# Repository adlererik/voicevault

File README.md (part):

# VoiceVault

**A dedicated encrypted voice device, being developed and tested in software before hardware is built.**

A phone can be an excellent communications modem and an unsafe place to handle a private conversation. VoiceVault explores a different boundary: put the microphone path, audio codec, encryption keys, verified contacts and call approval inside a separate device. Give the phone encrypted media to forward.

The intended adversary has **NSA-class capabilities**: both phones may already be completely compromised through Pegasus-like spyware, zero-day or zero-click exploits, and telecommunications and relays may be controlled by the attacker. **Supply-chain attacks are excluded from the current threat model.** The project starts after phone compromise; it does not attempt to prevent or reproduce the exploit that compromised the phone.

**Today:** working Rust voice simulations, hostile-phone processes, lifecycle security models, a live device-and-test dashboard and a linked Cortex-M33 diagnostic. **Destination:** a small independent voice endpoint with its own trusted display, wired headset audio, battery, inductive charging and a carefully isolated BLE connection to a phone. No physical VoiceVault device has been built.

[Project vision](docs/PROJECT_VISION.md) · [Architecture](docs/ARCHITECTURE.md) · [Threat model](docs/THREAT_MODEL.md) · [Every security control](docs/SECURITY_CONTROLS.md) · [Why these algorithms](docs/CRYPTOGRAPHY.md) · [Test evidence](docs/RESULTS.md) · [Hardware roadmap](docs/ROADMAP.md) · [Hybrid call security](docs/POST_QUANTUM.md)

## Hardware laboratory

The active **[standalone B0 design](hardware/rev-b/README.md)** is a custom **70 × 45 mm SMD PCB** using the identified Safe 7 core ICs, plus wired audio, physical microphone disconnect, offline microSD, trusted display/touch, battery/Qi circuits and separate MCU/radio debug interfaces. Native KiCad now contains **296 electrical components, 14 probe pads and four mounting holes**. KiCad is connected locally through MCP; **ngspice 47** runs the circuit experiments directly.

*Official FreeRouting 2.5.0 produced a complete-board SES checkpoint, imported into the live KiCad editor through kipy without changing any of the 314 placements. After copper refill, native KiCad reports 280 open connections, 33 layout errors and 100 warnings. [Actual routing result and DRC](hardware/evidence/2026-11-12/autoroute/README.md). Earlier checks cover MCU ball/function mapping and circuit correspondence; the circuit models include 799 passive/static cases. [Evidence and limits](hardware/evidence/2026-11-12/README.md)*

The subsequent [Quilter cloud trial](hardware/evidence/2026-11-13/quilter/routed-return/README.md) finished at **89% routed**, but native review with the original rules found **103 unfinished connections, 294 layout errors and 117 warnings**. It remains isolated for automatic repair and rerouting; it has not replaced the live board. Returned files, hashes, the screenshot and the complete native findings are preserved for review.

**Manufacturing remains blocked:** 280 connections remain unrouted and the latest native DRC failed. Exact sourcing and the HDI stackup need acceptance, and power/RF/audio/charging/isolation need physical qualification. The [circuit inventory](hardware/rev-b/circuit-inventory.csv) is not an approved JLCPCB BOM. [Cost comparison for four assemblies delivered to Sweden](hardware/rev-b/MANUFACTURING_COST.md). No board has been ordered or built. The earlier DK2 carrier and Nucleo assessment remain historical reference work in the [hardware laboratory](hardware/README.md).

## The idea: move the endpoint

An ordinary encrypted calling app processes plaintext on the phone. Once an attacker controls that operating system, network encryption alone cannot protect audio the operating system can already access.

VoiceVault's intended device owns the sensitive endpoint. Contacts are verified there, calls are approved there, and audio is encoded and encrypted there before reaching the phone. The phone carries encrypted records and necessary signaling; it does not become a trusted authority for identities, consent, keys, time, entropy or firmware.

This distinction depends on the physical audio path. The proposed host-phone arrangement includes removing its microphones and speakers, keeping voice on an external wired headset connected to VoiceVault, and validating remaining acoustic pickup paths. An unmodified compromised phone nearby can still record speech through its own microphone. [Why a separate device, and its limits](docs/DEVICE_RATIONALE.md)

*Architecture illustration. Analog audio and BLE are hardware targets; current calls use synthetic audio and bounded local IPC. Public signaling and transport metadata remain observable.*

## A real software foundation

The lab makes two endpoints conduct a simultaneous encrypted voice exchange through two hostile phone processes and a relay. It uses actual Opus and actual cryptography, produces recovered WAV files, injects delivery faults, and records results for inspection.

| Built and exercised | What it establishes |
|---|---|
| Two voice endpoints and three hostile transport processes | A concrete separation between trusted audio/key handling and untrusted delivery, under a trusted Linux host |
| Confirmed enrollment, pinned contacts and signed invitations | Explicit identity, consent, replay and accepted-call binding rules |
| Real Opus → Noise encryption → hostile transport → authentication → decode | An executable media pipeline, including loss and malformed-input handling |
| Stored-contact, entropy, radio and offline-update models | Testable device-local policy before selecting physical chips |
| The same trusted crates compiled without `std` and linked for Cortex-M33 | Functional CPU execution and measured memory fit under a named capacity budget |
| An event-backed dashboard with searchable individual results | Visible checks, named test outcomes, attack traces and saved replays |

A tested model is not a finished hardware protection. The [assurance case](docs/ASSURANCE.md) states which assumptions each result depends on.

## The threat model and the protections

The attacker may observe, drop, replay, modify, reorder, delay and inject traffic; collude across both phones and relays; impersonate contacts; flood ingress; and try to turn malformed messages into unauthorized device actions. The design also tests a malicious authenticated peer, because having a valid key does not make compressed audio harmless.

| Attack or failure | Protection in the software model | Boundary |
|---|---|---|
| Intercept or modify voice | ChaCha20-Poly1305 under authenticated Noise transport keys | Trusted endpoints and sound implementations are assumed |
| Substitute a peer during enrollment | Noise XX, signed identity/DH records, full transcript comparison and confirmation on both sides | Trusted local comparison is required; hardware UI is future work |
| Spoof a contact or call invitation | Pinned Ed25519 identity, recipient binding, boot challenge, expiry and persisted counters | Invitation metadata itself is not confidential |
| Reuse a different invitation for an authenticated call | The hybrid Noise prologue binds the signed offer and acceptance and both verified identities | Local approval remains separate from remote signaling |
| Save encrypted calls for future quantum decryption | Fresh X25519 and ML-KEM-768 establish each call, with the hybrid suite required | Depends on the hybrid construction, trusted endpoints and erasure |
| Replay media or poison the replay window | Monotonic sending, directional keys, authenticated counter/slot checks and a bounded replay bitmap | Invalid input cannot commit incoming replay state |
| Activate audio through the phone | Local consent plus encrypted Confirm/Ready; no radio mic/consent opcode | Actual headset and physical disconnect still need validation |
| Infer speech or silence from record length | CBR Opus, DTX off, fixed 128-byte records and encrypted filler | Call boundaries, timing errors, location and correlation remain visible |
| Exhaust queues or force a burst after a stall | Bounded ingress, assembly and jitter queues; expiry; absolute deadlines; missed slots discarded | A hostile network can still deny service |
| Roll back stored contacts or signaling counters | Owner-bound AEAD snapshots tied to a protected monotonic generation | Protected storage is modeled, not a chip driver |
| Push firmware through the phone | No remote updater; locally authorized signed-image policy | Physical boot/update enforcement remains future hardware work |
| Install an old, corrupt or wrong-device image | Target/version/hash/signature checks, protected floor, two banks and readback | Real flash and counter atomicity are unmeasured |
| Interrupt an offline update | Preserve the active bank, write header last, verify before boot/version handoff | Tests cover modeled write cuts and selected torn writes |
| Weaken randomness through the phone | Onboard-only entropy-source interface, failure checks and two-source policy | Hardware entropy quality and independence need measurement |
| Keep using a closed or expired session | Irreversible close, owned key destruction, bounded media epoch and fresh handshake | Complete erasure and seamless renewal remain open |

The [complete control register](docs/SECURITY_CONTROLS.md) links each protection to its code, evidence, assumptions and remaining hardware work.

## Why these cryptographic choices?

| Choice | Role and reason |
|---|---|
| **X25519** | Compact Diffie–Hellman key exchange with fresh per-call ephemeral secrets; separate from signing identities |
| **ML-KEM-768** | Adds a fresh post-quantum secret for each call using the portable `libcrux-ml-kem` implementation |
| **Ed25519** | Signed identities, contact bindings, invitations and offline-image authorization |
| **ChaCha20-Poly1305** | Established authenticated encryption for voice and stored snapshots; suitable for portable software implementations |
| **BLAKE2s** | A 32-bit-oriented hash for the selected Noise suite, domain-separated bindings and firmware digests |
| **Noise's HMAC/HKDF-BLAKE2s** | An established transcript-bound key schedule and separate transport keys for each direction |
| **Noise XX / KKhfs through Snow** | XX for first enrollment and the experimental hybrid KK modifier for calls between pinned contacts |
| **Opus** | Practical speech compression; hard CBR and no DTX work with the outer fixed-size envelope |
| **Rust with `no_std` integration** | Safe parsing/state code and bounded interfaces that can migrate toward embedded firmware |

The hybrid suite is required for new calls. Both peers authenticate the full exchange and its algorithm suite before local consent and encrypted confirmation open audio. ML-KEM-768 is an explicit exception to the owner’s preference to avoid NIST algorithms where practical. [Protocol and wire format](docs/POST_QUANTUM.md) · [Cryptographic rationale](docs/CRYPTOGRAPHY.md)

## Evidence you can inspect

The hybrid v2 run on **2026-11-11** passed **all 11 required groups and 48 checks**. The suite recorded 68 named outcomes, including five bounded Kani checks, and ran eight fuzz campaigns for at least 120 seconds each. It also checked 80 ML-KEM-768 vectors. The altered-startup scenario verifies that a compromised phone cannot open either audio path by modifying the key exchange.

| Recorded result | Observation |
|---|---|
| Real encrypted audio | Both directions recovered generated audio through two hostile phone processes and a relay |
| Cortex-M33 execution | Hybrid startup, fragmentation and 32 Opus frames executed in QEMU |
| Linked image and observed stack | 863,104 bytes of a 983,040-byte slot and 84,876 bytes of a 131,072-byte stack reserve |
| Reference memory budget | 37,500 bytes unassigned after static state and stack/display/driver reservations |

[Latest raw results](docs/evidence/hybrid-v2/) · [What each fuzz target tests](docs/FUZZING.md) · [All recorded runs](docs/RESULTS.md) · [Embedded fit](docs/PLATFORM.md)

*Actual dashboard capture during hybrid handshake fuzzing. The device panels show the earlier live call in the same run. [Live call capture](docs/screenshots/command-deck-live-laptop.png) · [Historical full-suite completion](docs/screenshots/voicevault-complete.png)*

## See what is happening as it happens

The UI opens at **http://127.0.0.1:8765/** for every run. Two device panels show identity/contact verification, invitation authentication, call establishment, encrypted media, receiver rejection and audio playout/concealment. Both hostile phones and the relay are shown between them. The test area reports every scheduled check, individual Rust tests, all twelve Opus vectors, each bounded proof and actual fuzzing counters as their harnesses report them.

`./lab demo --seconds 30` gives two visible 30-second normal/fault calls. Click **Listen live** to monitor actual decoded synthetic tones. Choose either receiver or both; sound is off by default. Device cards, graphical phones, packet/rejection flashes, a recent-event ticker and compact check/fuzz displays now occupy the top observation deck. `./lab watch` runs the complete verification suite; `./lab ui` reopens the persistent page. Refresh reconstructs the current run, reconnect resumes events, and a new published run resets the display. Compilation, proofs and fuzzing are shown as checks rather than invented device traffic. Scored timing keeps graphics still and labels its buffered packet traces recorded. A running test is never displayed as a pass merely because it started. [How the dashboard works](docs/LIVE_DASHBOARD.md)

## Toward the physical device

The intended device has a trusted color display and controls, analog headset jack, independent battery, inductive charging and a separate BLE controller. Persistent secrets and protected state should use appropriate secure-element capabilities. A small protected first-stage verifier and physically initiated offline updates are part of the intended boot design. The inspiration is the Safe 7 separation of host and sensitive operations; this is an independent voice design with different workloads and requirements.

The next hardware work is to finish the standalone B0 placement and routing, review power/clock/RF/return paths, finalize exact sourcing and prepare a controlled bring-up plan. Focused simulations guide the measurements needed on physical prototypes. Real-time audio, radio containment, hardware entropy, durable storage, trusted UI and acoustic leakage need physical evidence. Decentralized signaling, possibly through interchangeable Nostr relay adapters, remains a future investigation. The proposed clear glitter enclosure and signed reference photos are separate physical tamper-evidence research.

[Device vision](docs/PROJECT_VISION.md) · [Hardware comparison](docs/DEVICE_RATIONALE.md) · [Safe 7 reference and prototype plan](docs/HARDWARE_PLAN.md) · [Roadmap and decision gates](docs/ROADMAP.md)

## Try the software lab

```sh
git clone https://github.com/adlererik/voicevault.git
cd voicevault
./lab help
./lab demo
./lab watch --out /absolute/path/to/an/empty/directory
./lab ui       # reopen the same persistent local dashboard
./lab status
./lab replay
```

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
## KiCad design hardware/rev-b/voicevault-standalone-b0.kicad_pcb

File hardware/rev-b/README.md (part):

# VoiceVault standalone prototype B0

**Routing in progress — not a working or fabrication-ready PCB.**

[Quilter routing and native review (13 November)](QUILTER_ROUTING.md): the full cloud trial finished at 89% routed. Native review found 103 unfinished connections, 294 layout errors and 117 warnings, so the result is isolated for repair and has not replaced the live PCB. Six placement candidates, input hashes and rejected experiments are also preserved.

VoiceVault moves plaintext voice, keys, contacts and call approval into a dedicated device. An already compromised phone carries encrypted records over BLE. This custom rectangular SMD board uses the identified **Trezor Safe 7 TS7 rev_D core ICs**, with added wired headset audio, physical microphone disconnect, offline microSD and separate computer-debug connections. It replaces the earlier development-board carrier as the active hardware design.

The current native KiCad project contains **296 electrical components, 14 board-only probe pads and four mounting holes** on a provisional **70 × 45 mm**, six-layer, 1.0 mm board. Components are placed on both sides. The latest complete-board autorouter checkpoint **fails native DRC: 280 connections remain unrouted, with 33 layout errors and 100 warnings**; exact sourcing and HDI stackup are unresolved, and no physical board has been tested. [Machine-readable status](STATUS.json) · [Recorded evidence and images](../evidence/2026-11-12/README.md)

*Native KiCad exports, front and rear. RF copper and ground pours are present; most signal and power routing remains incomplete.*

## Open and inspect

From the repository root, run `./hardware/open`. The launcher opens one PCB editor and reuses it to limit memory use. Open `voicevault-standalone-b0.kicad_pro` in KiCad to inspect the root schematic and its **18 child sheets**. Keep the large schematic/3D viewers closed when running routing studies on this computer.

KiCad 10.0.8 uses the local `voicevault-kicad` MCP connection through its official IPC API. Circuit simulation uses **ngspice 47 directly**, preserving actual netlists, logs and measurements. MCP is useful for editor interaction; it is not required to run a command-line simulator. [Tool setup](../README.md)

```sh
./hardware/check --design-only --spice
```

This runs native schematic/pad/net checks, ST ball/function comparisons, ERC/DRC, an antenna-rule negative control, **799 ngspice model cases**, and the explicit power-allocation study. Exit 0 with `--design-only` means the available checks passed. The report still says **manufacturing blocked**. Without that option, exit 2 preserves the blocked release verdict. Exit 1 means a check failed. The historical carrier checks remain available as `./hardware/check --rev-a --design-only`.

## Circuit architecture

| Area | Current circuit intent |
|---|---|
| Trusted compute | STM32U5G9ZJJ6Q, UFBGA144, with local clocks, reset, decoupling and internal-SMPS network. The local symbol restores two power balls missing in the installed library. All 144 ball names and 29 selected peripheral functions are compared with separately pinned ST data. |
| Power and battery | nPM1300 dual 200 mA bucks/charger; USB power-only entry, diode-isolated Qi entry, protected battery connector and external cell-temperature input. USB has no D+/D− contacts. Charging configuration and thermal qualification remain open. |
| Secure elements | TROPIC01 and OPTIGA Trust M on MCU-only buses with local power gates. These circuits do not demonstrate lifecycle configuration, entropy quality or secret protection on real silicon. |
| Hostile radio boundary | nRF52832-CIAA with separate SWD and radio power, fixed-direction SN74AXC4T774 bridges, reset control and default-disabled interface. UART carries bounded records; the radio has no audio, secure-element or MCU-debug wires. Electrical fault containment still needs bench tests. |
| Voice | TLV320AIC3204, SAI1 full duplex, dedicated switched audio regulator, CTIA 3.5 mm headset jack, headphone DC-blocking networks, ESD parts and a physical microphone disconnect. All codec controls stay on the trusted MCU side. |
| Trusted interface | Newhaven 240 × 320 display/touch candidate, local reset/update buttons and DRV2624 haptic driver. These require new VoiceVault drivers; this is not the Safe 7 private display assembly. |
| Offline updates | Locally powered microSD SPI interface with default-disabled signal bridge. Signed-image, rollback and interrupted-update policies exist in the software model; they have not been ported and qualified as this board's boot/update firmware. |
| Qi | STWLC38 receiver, coil resonance/rectifier components, thermal sensing and disable path. Its host-control bus is separate from PMIC and secure-element buses. Matching, configuration, charging and temperature behavior are unqualified. |
| NFC | ST25R3916B with dedicated regulator, bridges and matching network; default-off intent. Firmware must require an explicit local enrollment action. An NFC transport is not itself proof of contact identity. |
| Bench access | Main STDC14 and independent Nordic SWD headers, 14 probe pads and removable audio-current link. Prototype debug access deliberately exposes memory/firmware to trusted lab equipment. |

Read [circuit and power review](CIRCUIT_REVIEW.md), [computer connection and bring-up](DEBUG_AND_BRINGUP.md), and [display/battery adaptations](DISPLAY_BATTERY_CANDIDATES.md) before hardware work.

## Exact reference and differences

The source is pinned to trezor/trezor-hardware commit `d99ad42320a19875c124445195fa56f0dbaff6db`. The actual Safe 7 MCU is **STM32U5G9ZJJ6Q in UFBGA144**, not the LQFP144 STM32U5G9ZJT6Q on the DK2 reference board. The earlier DK2 pin allocations and hardware measurements cannot be assumed to apply to this PCB. Actual silicon revision is not yet verified.

The ten core selections are STM32U5G9ZJJ6Q, nPM1300-CAAA, TPS3420DDRYR, STWLC38JRM, nRF52832-CIAA, ST25R3916B-BWLT, SLS32AIA010MKUSON10XTMA2, TPS61062YZFR, DRV2624YFFR and the TROPIC01 family. TPS61062's `R` suffix selects tape/reel packaging. **TROPIC01's orderable silicon/provisioning revision remains unresolved. OPTIGA's reference order code is NRND.** [Core source table](core-parts.csv)

The published Safe 7 release contains PDFs and board views; it does not supply a complete editable manufacturing project or its private display/battery assemblies. This is a new VoiceVault layout, with catalogue display/battery candidates and added audio/card/debug circuitry. AO3401A power-gate FETs are an explicit adaptation from the reference CSD25501F3. New crystals, antenna/coil geometry, power loads and enclosure need their own validation. No Trezor factory identities, attestation keys or certification are reproduced.

## What the evidence establishes

The native export and actual PCB pads agree for 1,026 schematic-connected nodes and 124 intentional NC pins. The schematic's 323 exported net records include those virtual NC records; the PCB has **199 named copper nets**. The saved pre-autoroute check had zero ERC issues and zero layout violations. After the complete-board SES import and copper refill, native KiCad reports **280 open connections, 33 layout errors and 100 warnings**. The detailed list and independent full ratsnest both report 280. [Final native result](../evidence/2026-11-12/autoroute/README.md).

The antenna restriction is tested on a copy: headless KiCad rejects an unrelated track and a ground via inside the reserved area, and permits the RF-feed track. The live design is checked to remain unchanged. This verifies a CAD rule, not antenna performance or isolation from a physical attacker.

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
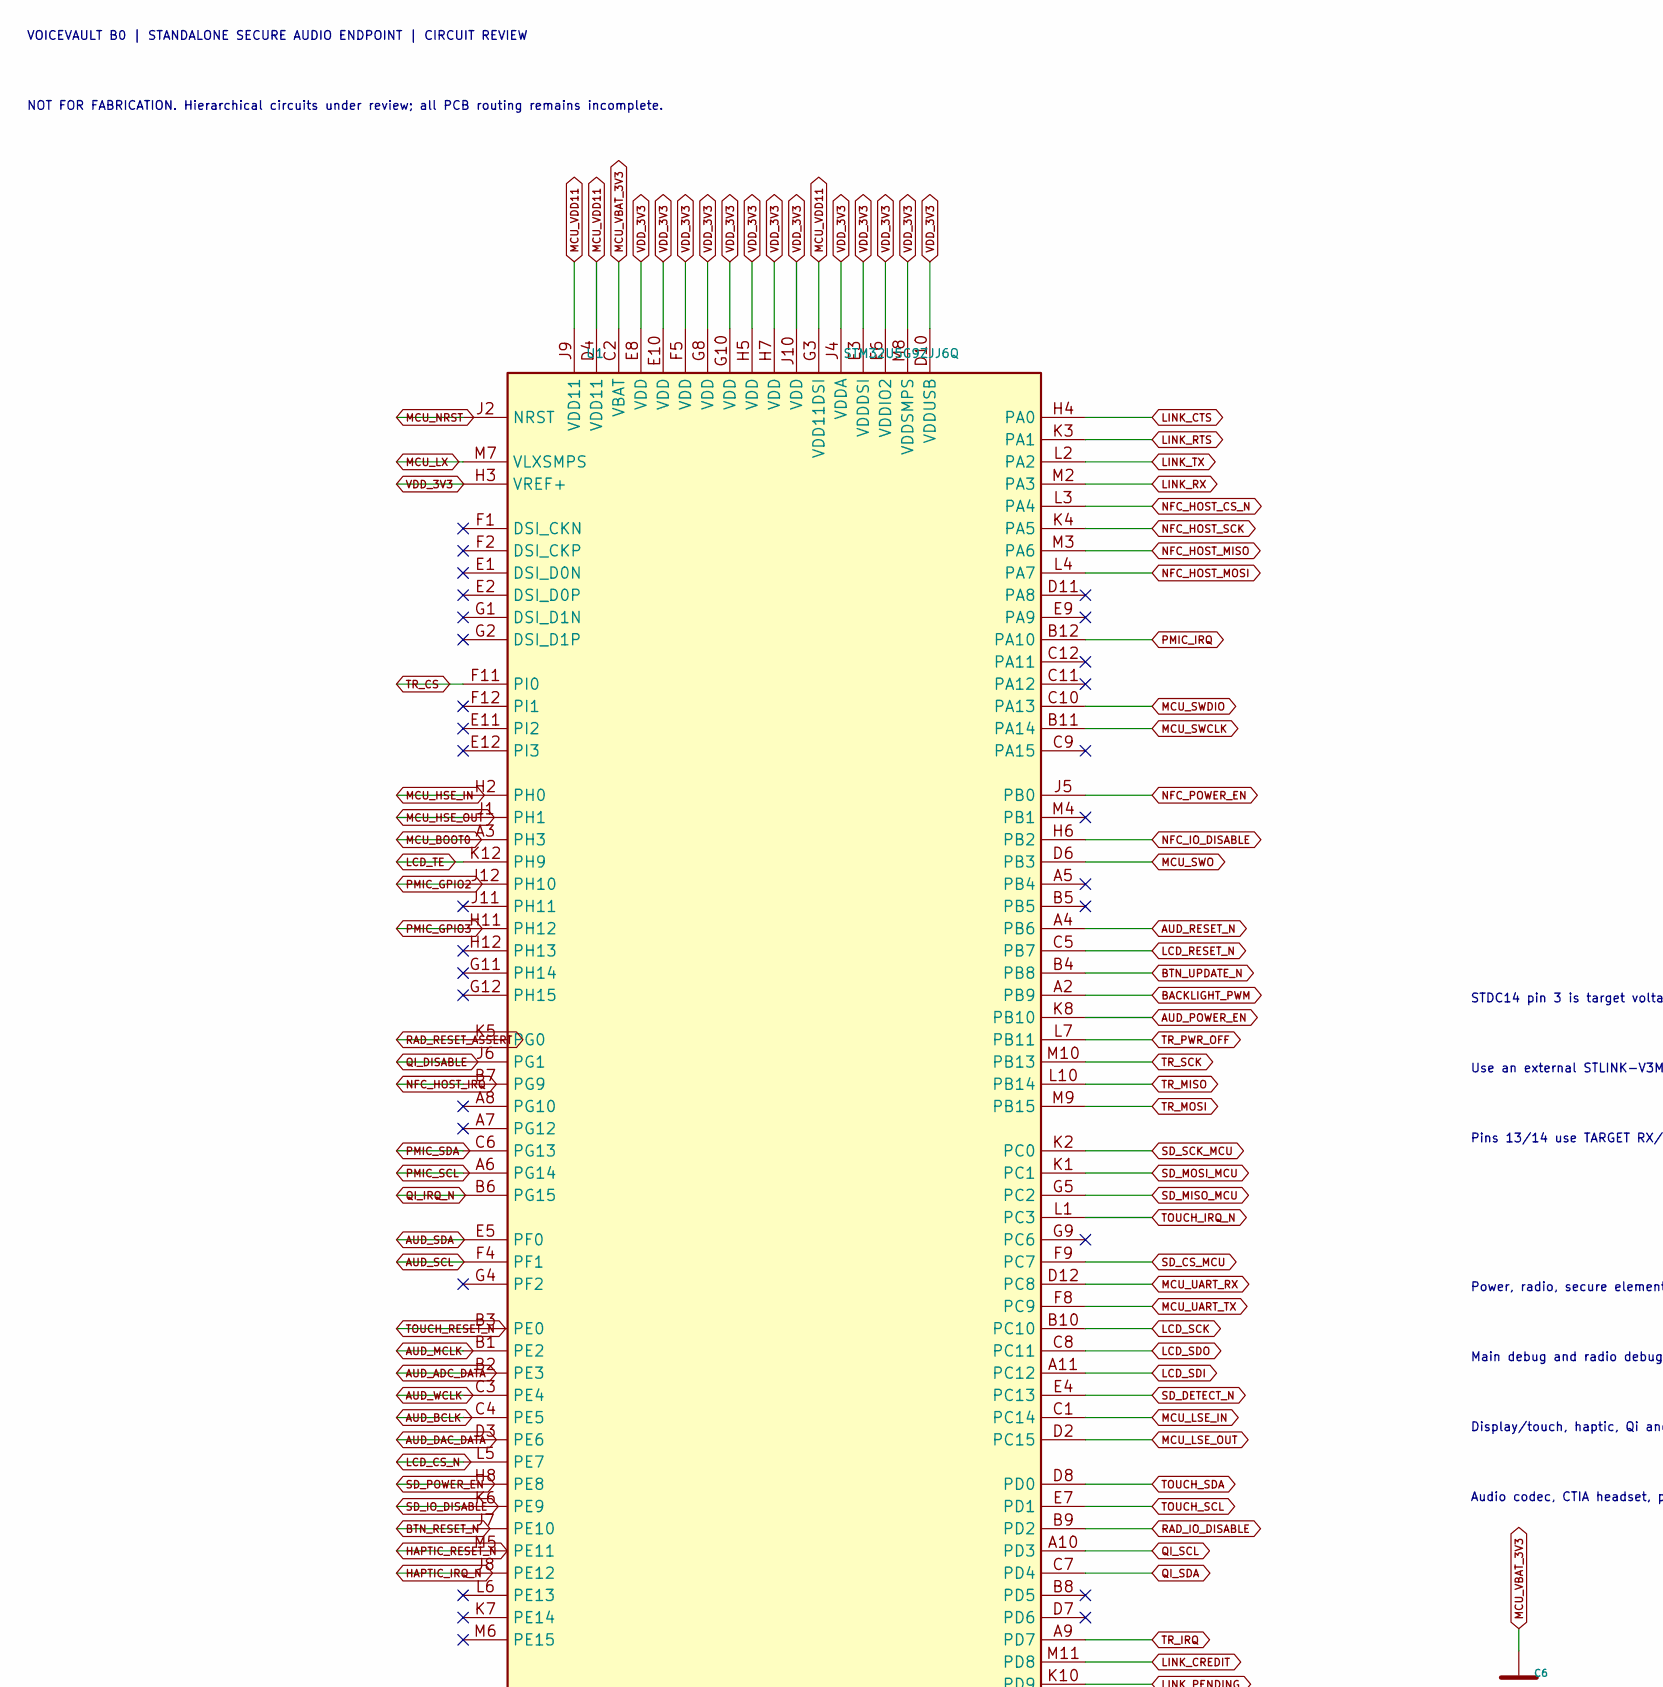
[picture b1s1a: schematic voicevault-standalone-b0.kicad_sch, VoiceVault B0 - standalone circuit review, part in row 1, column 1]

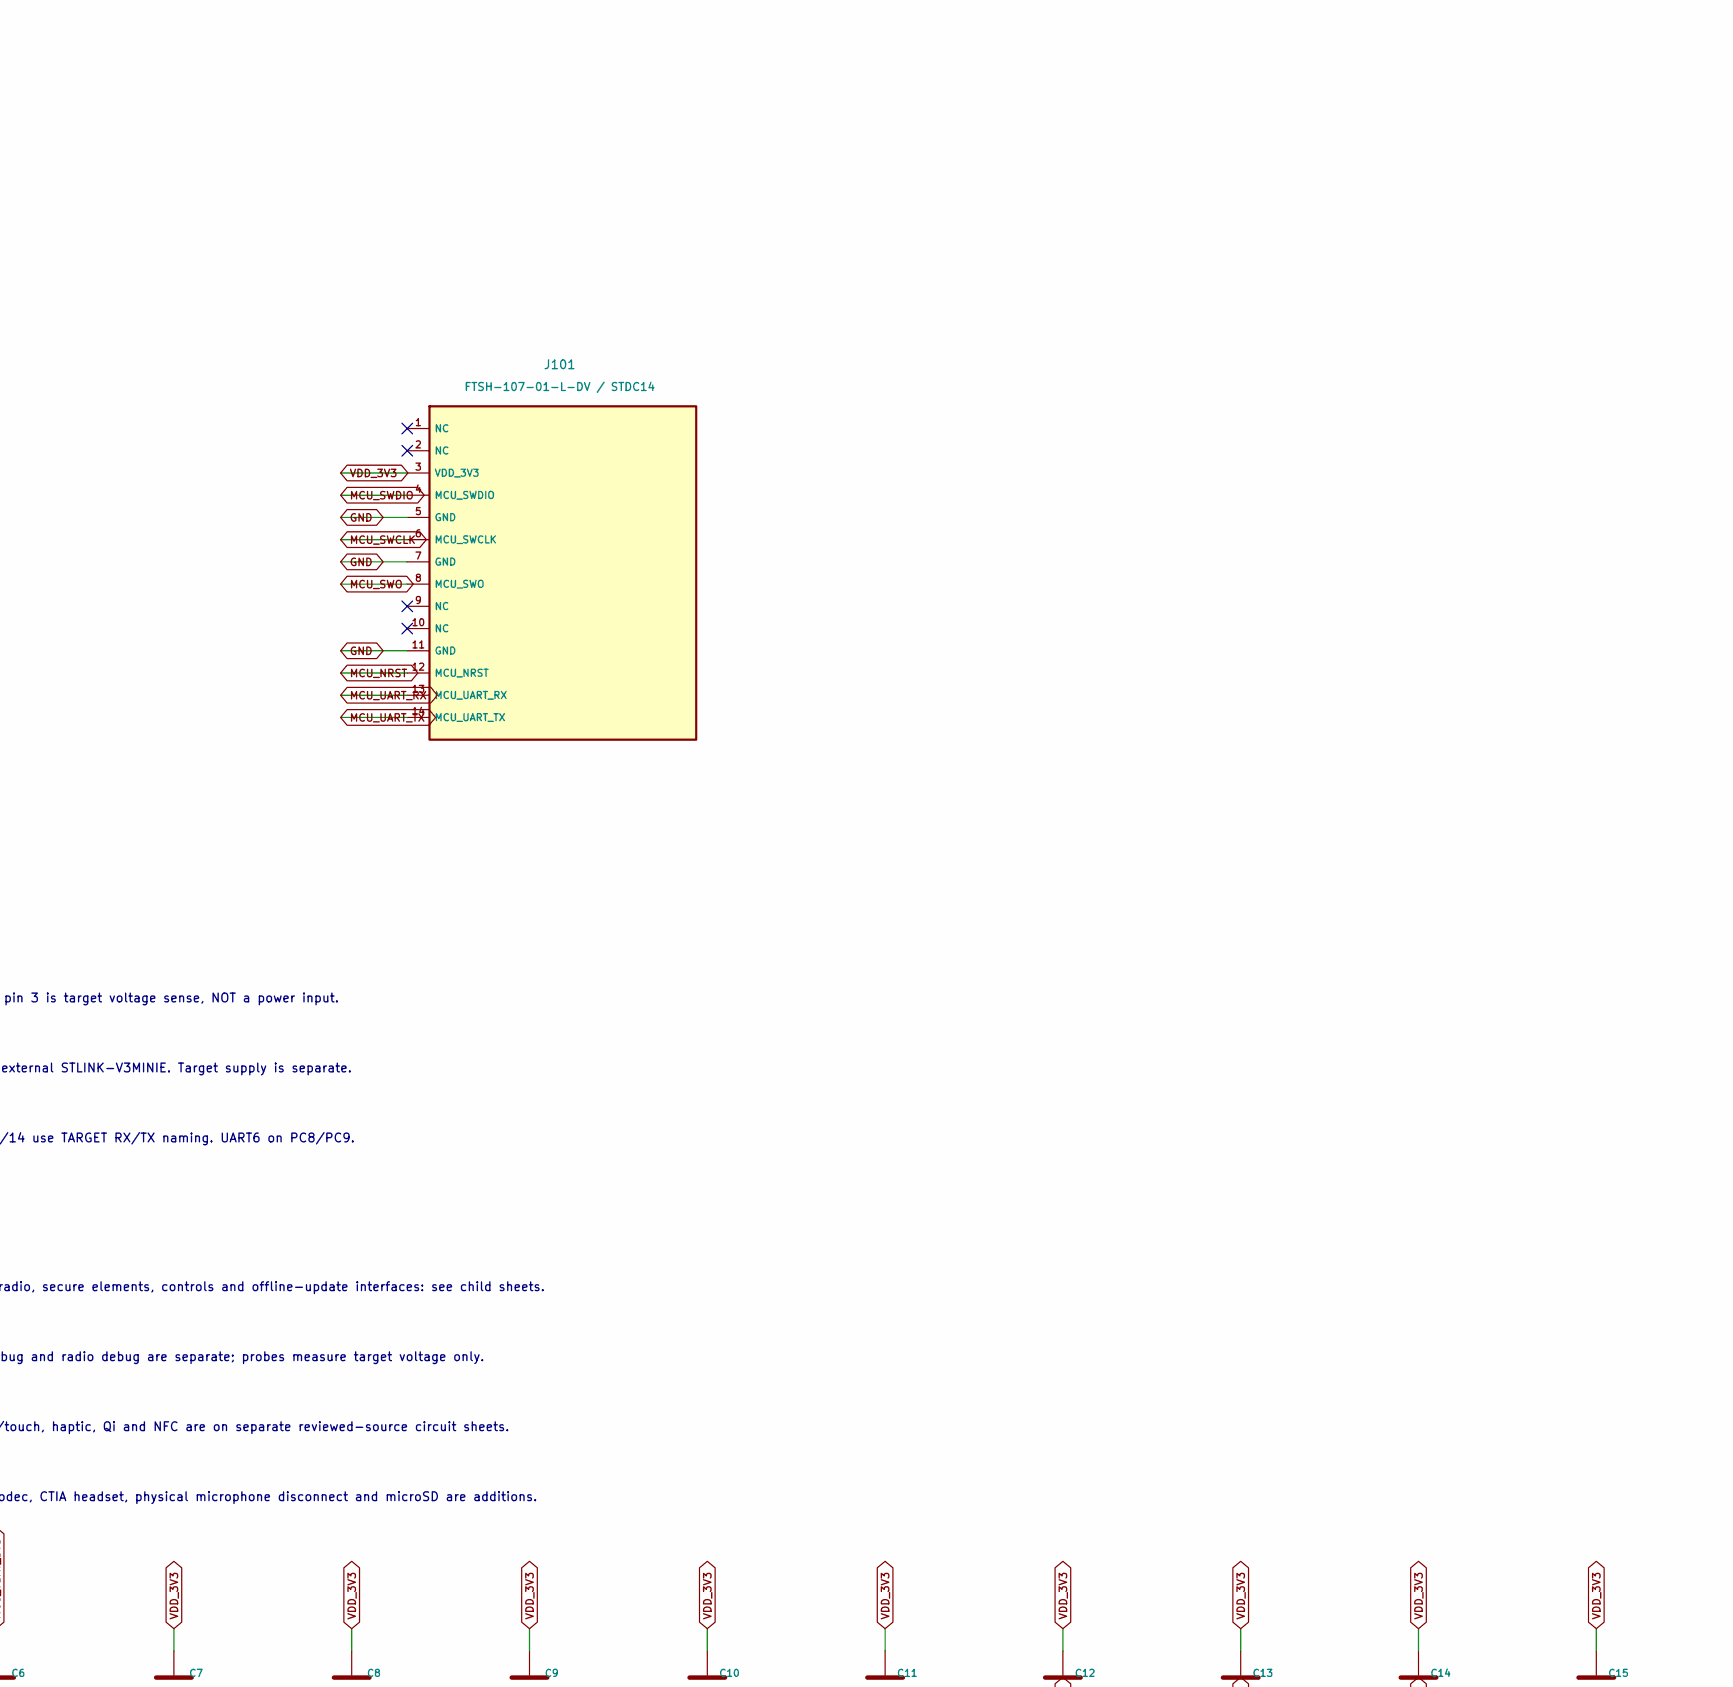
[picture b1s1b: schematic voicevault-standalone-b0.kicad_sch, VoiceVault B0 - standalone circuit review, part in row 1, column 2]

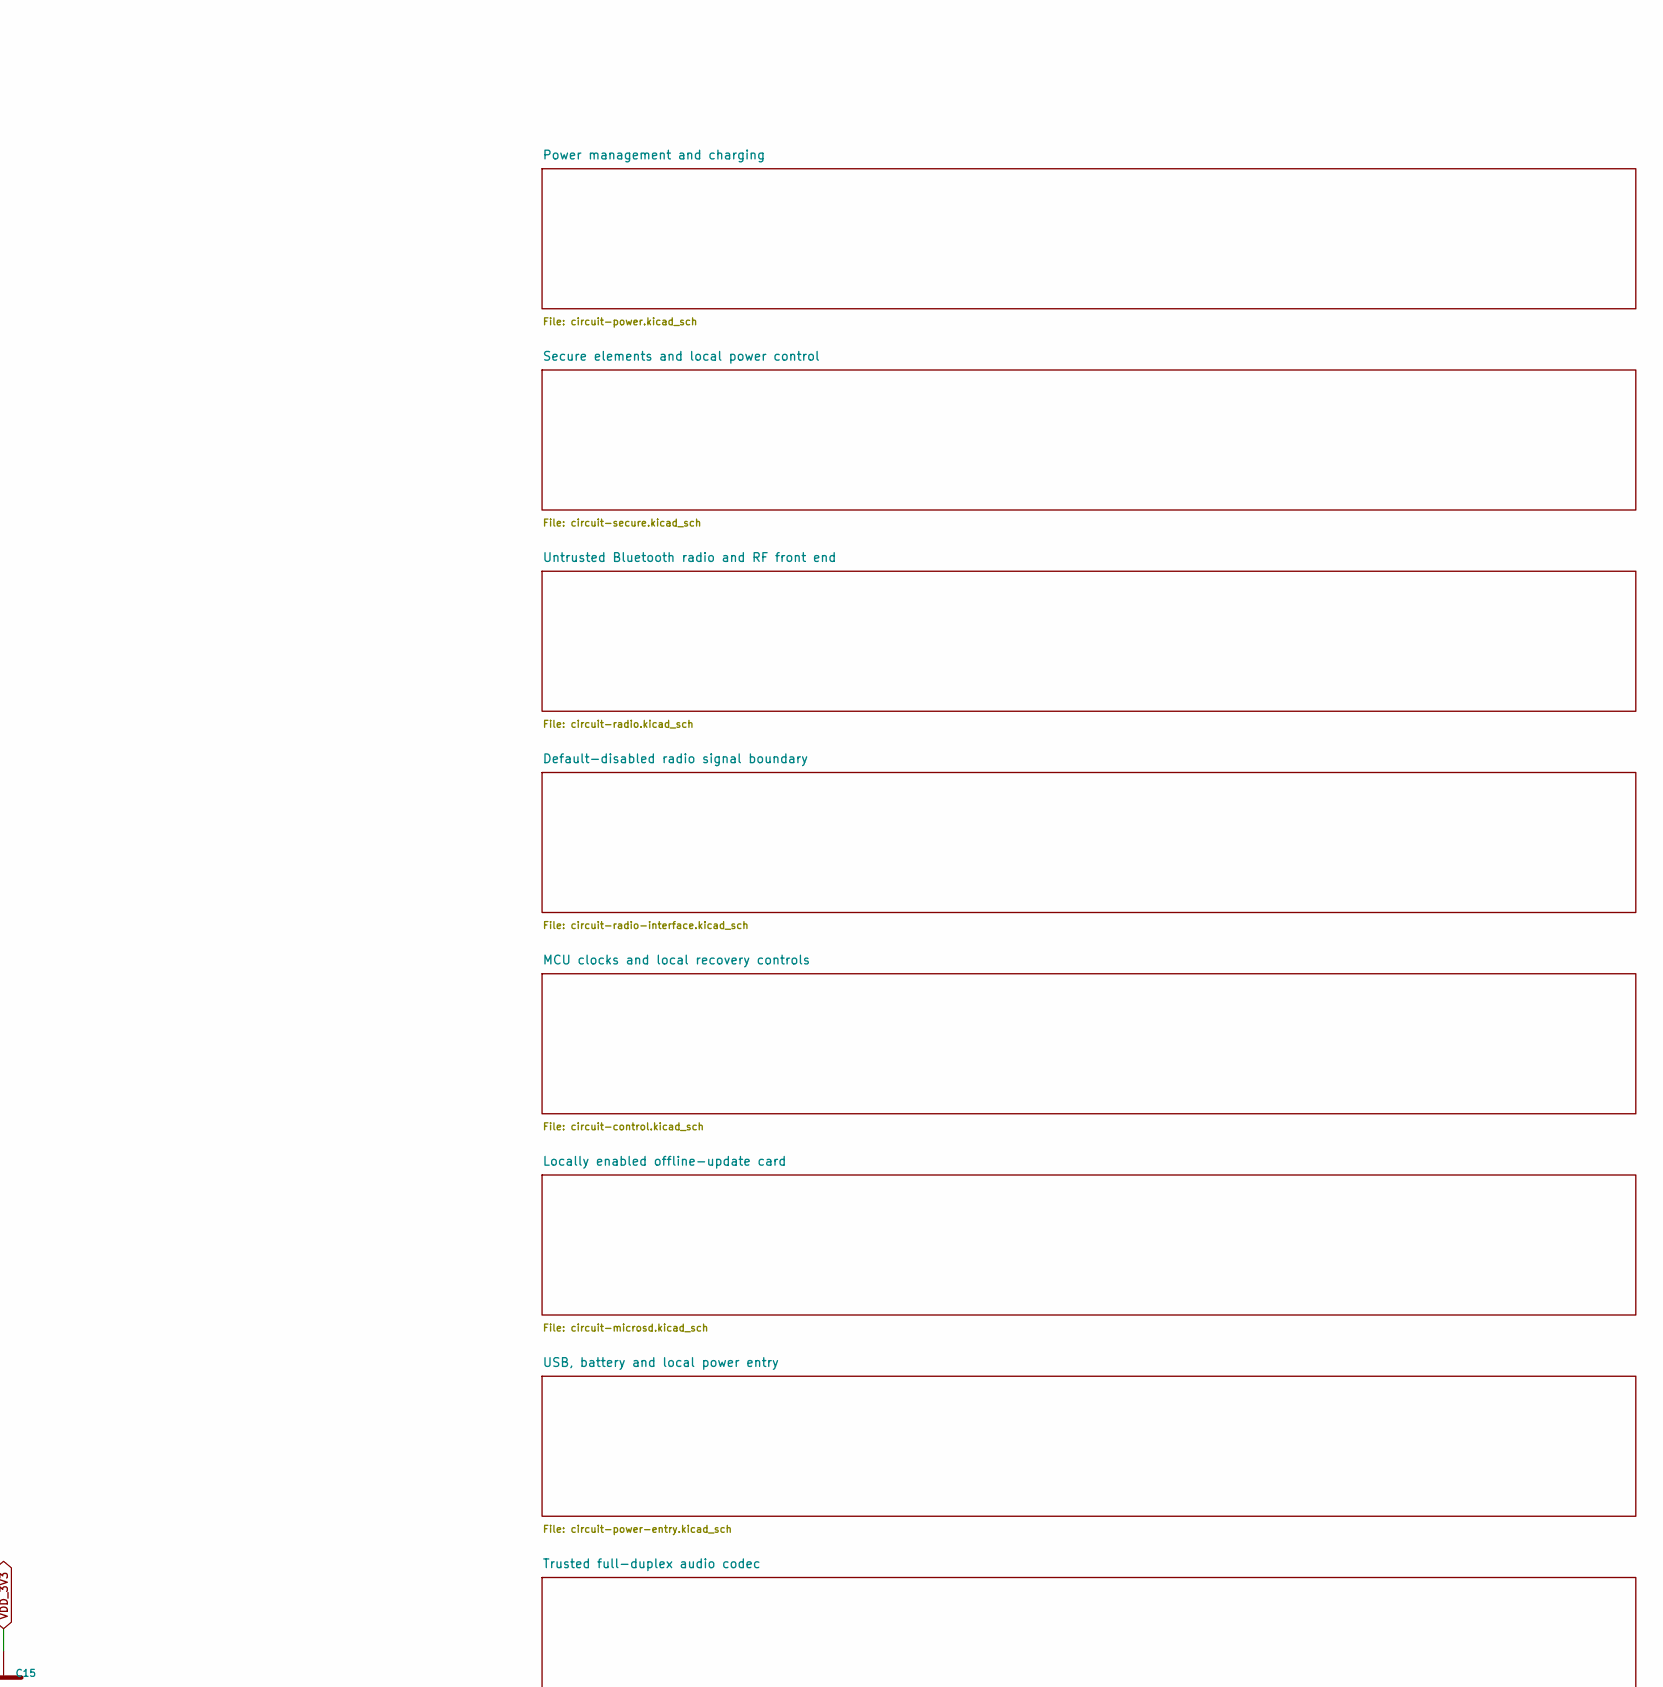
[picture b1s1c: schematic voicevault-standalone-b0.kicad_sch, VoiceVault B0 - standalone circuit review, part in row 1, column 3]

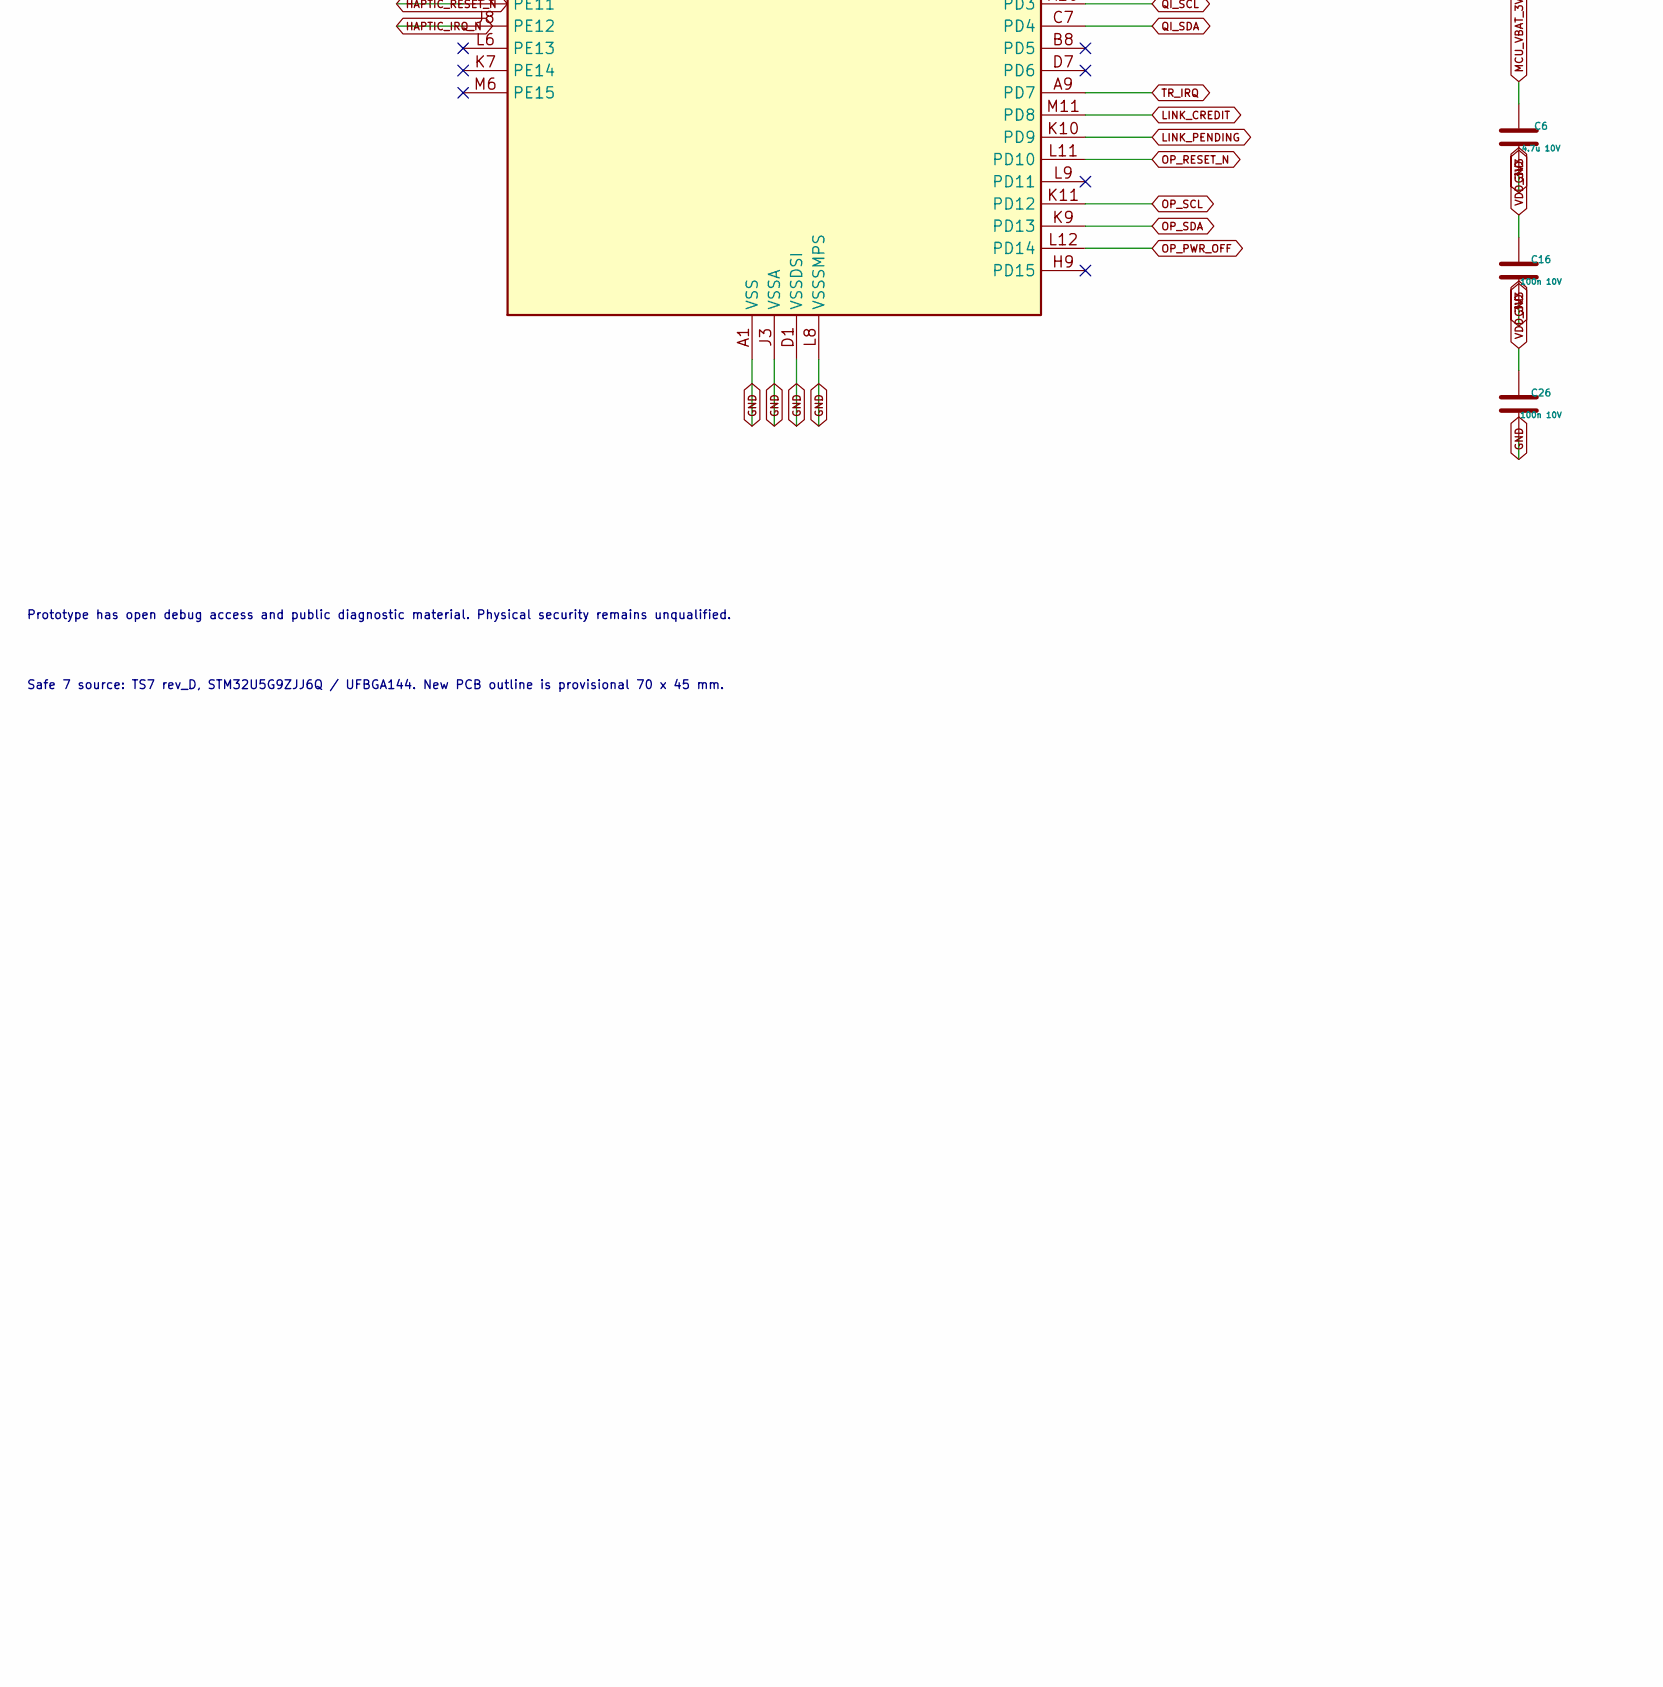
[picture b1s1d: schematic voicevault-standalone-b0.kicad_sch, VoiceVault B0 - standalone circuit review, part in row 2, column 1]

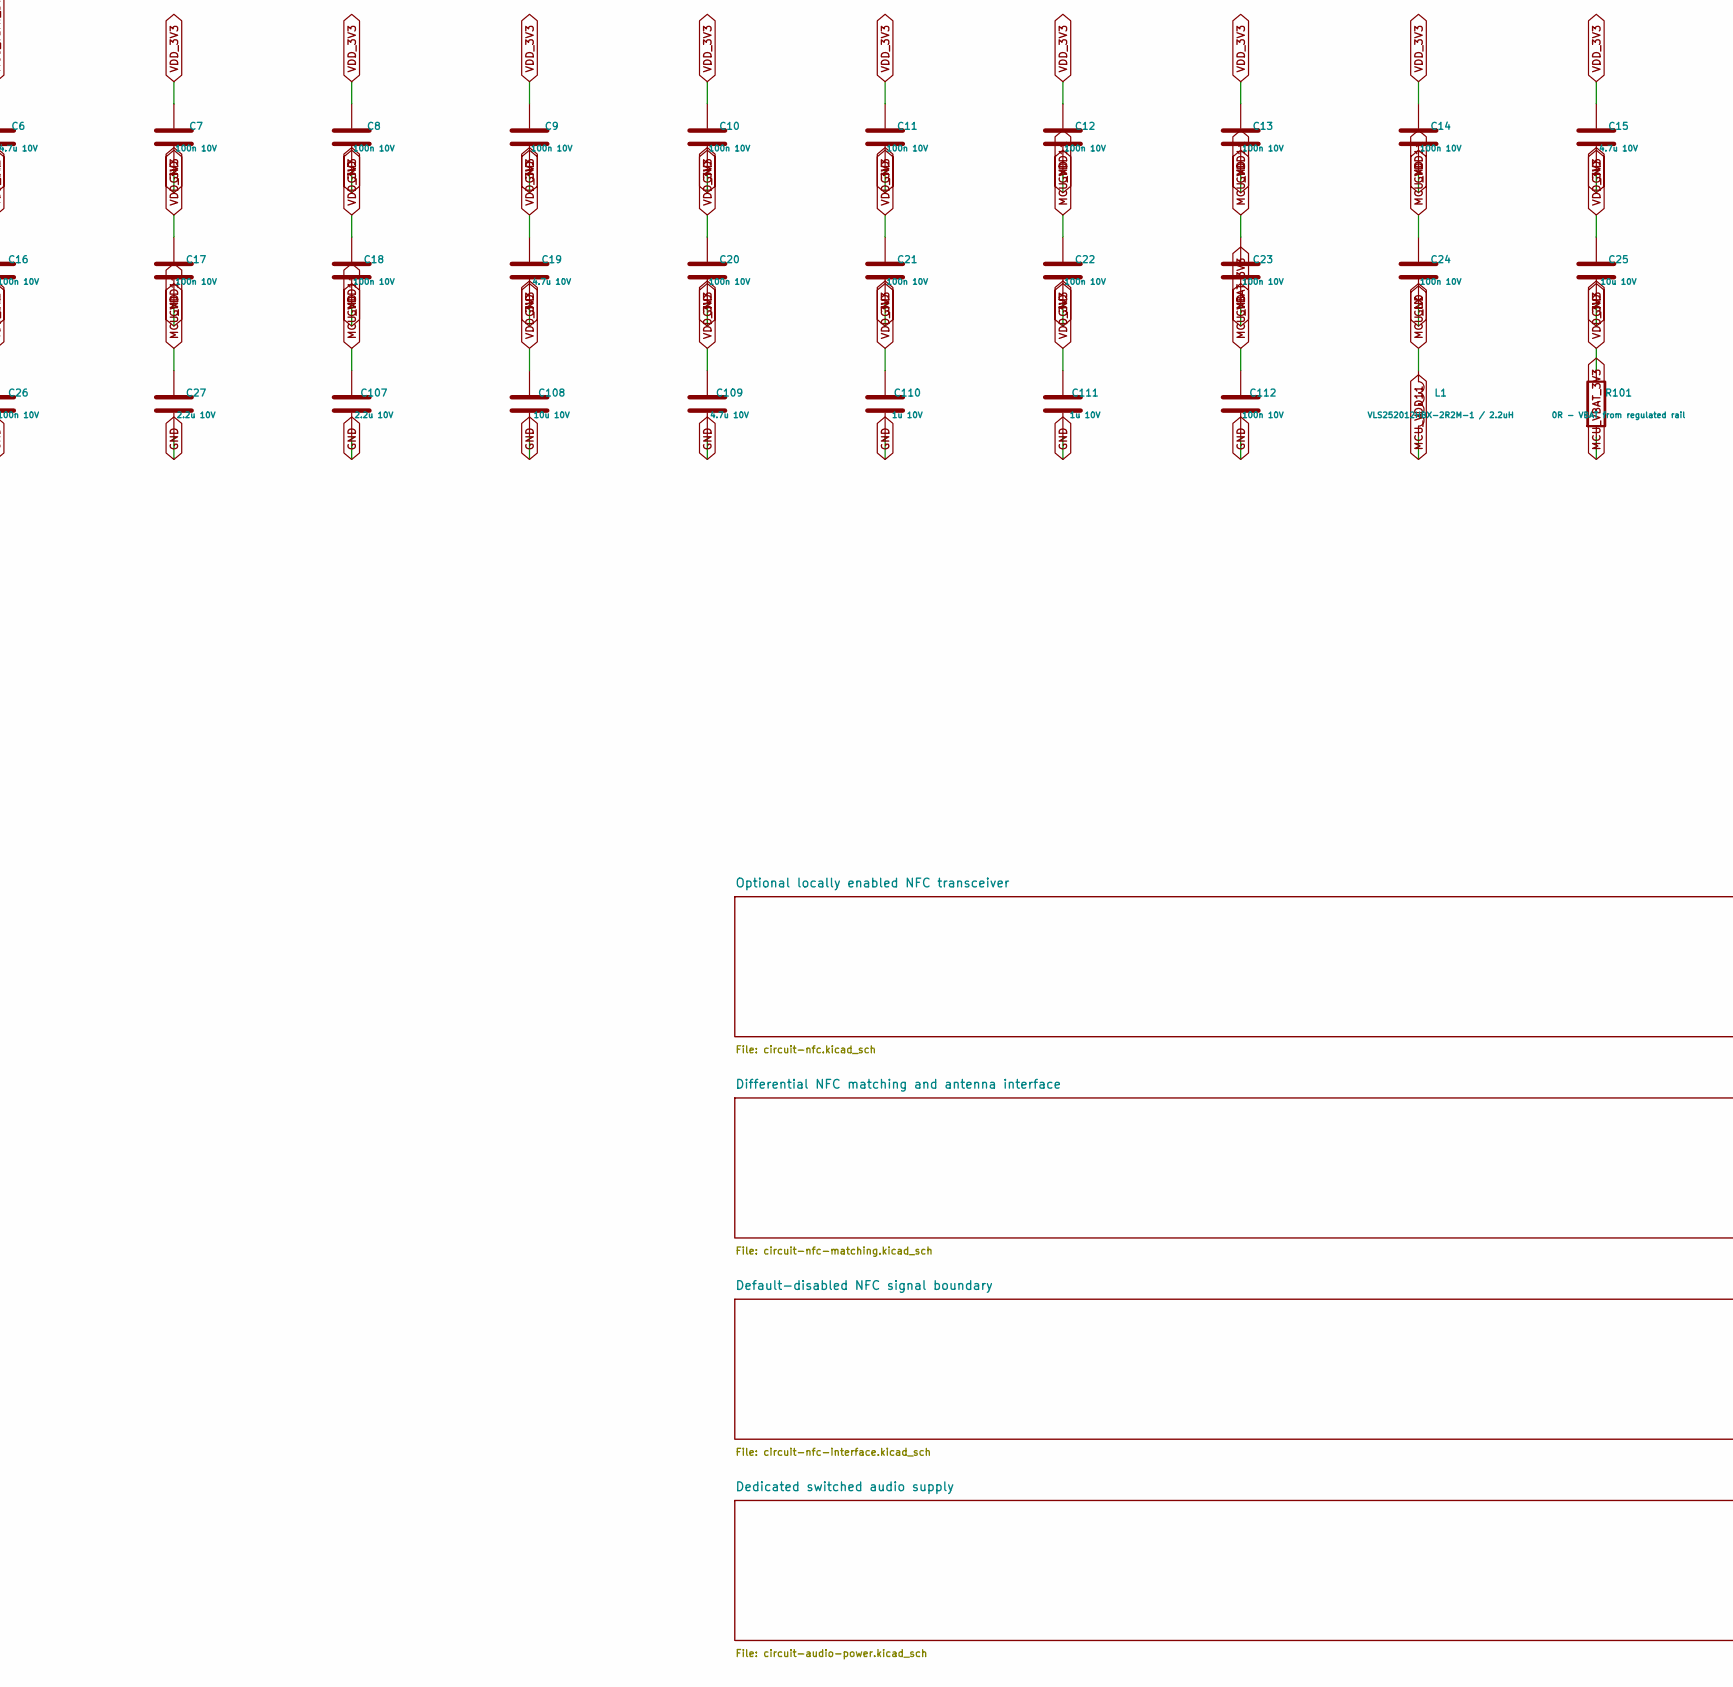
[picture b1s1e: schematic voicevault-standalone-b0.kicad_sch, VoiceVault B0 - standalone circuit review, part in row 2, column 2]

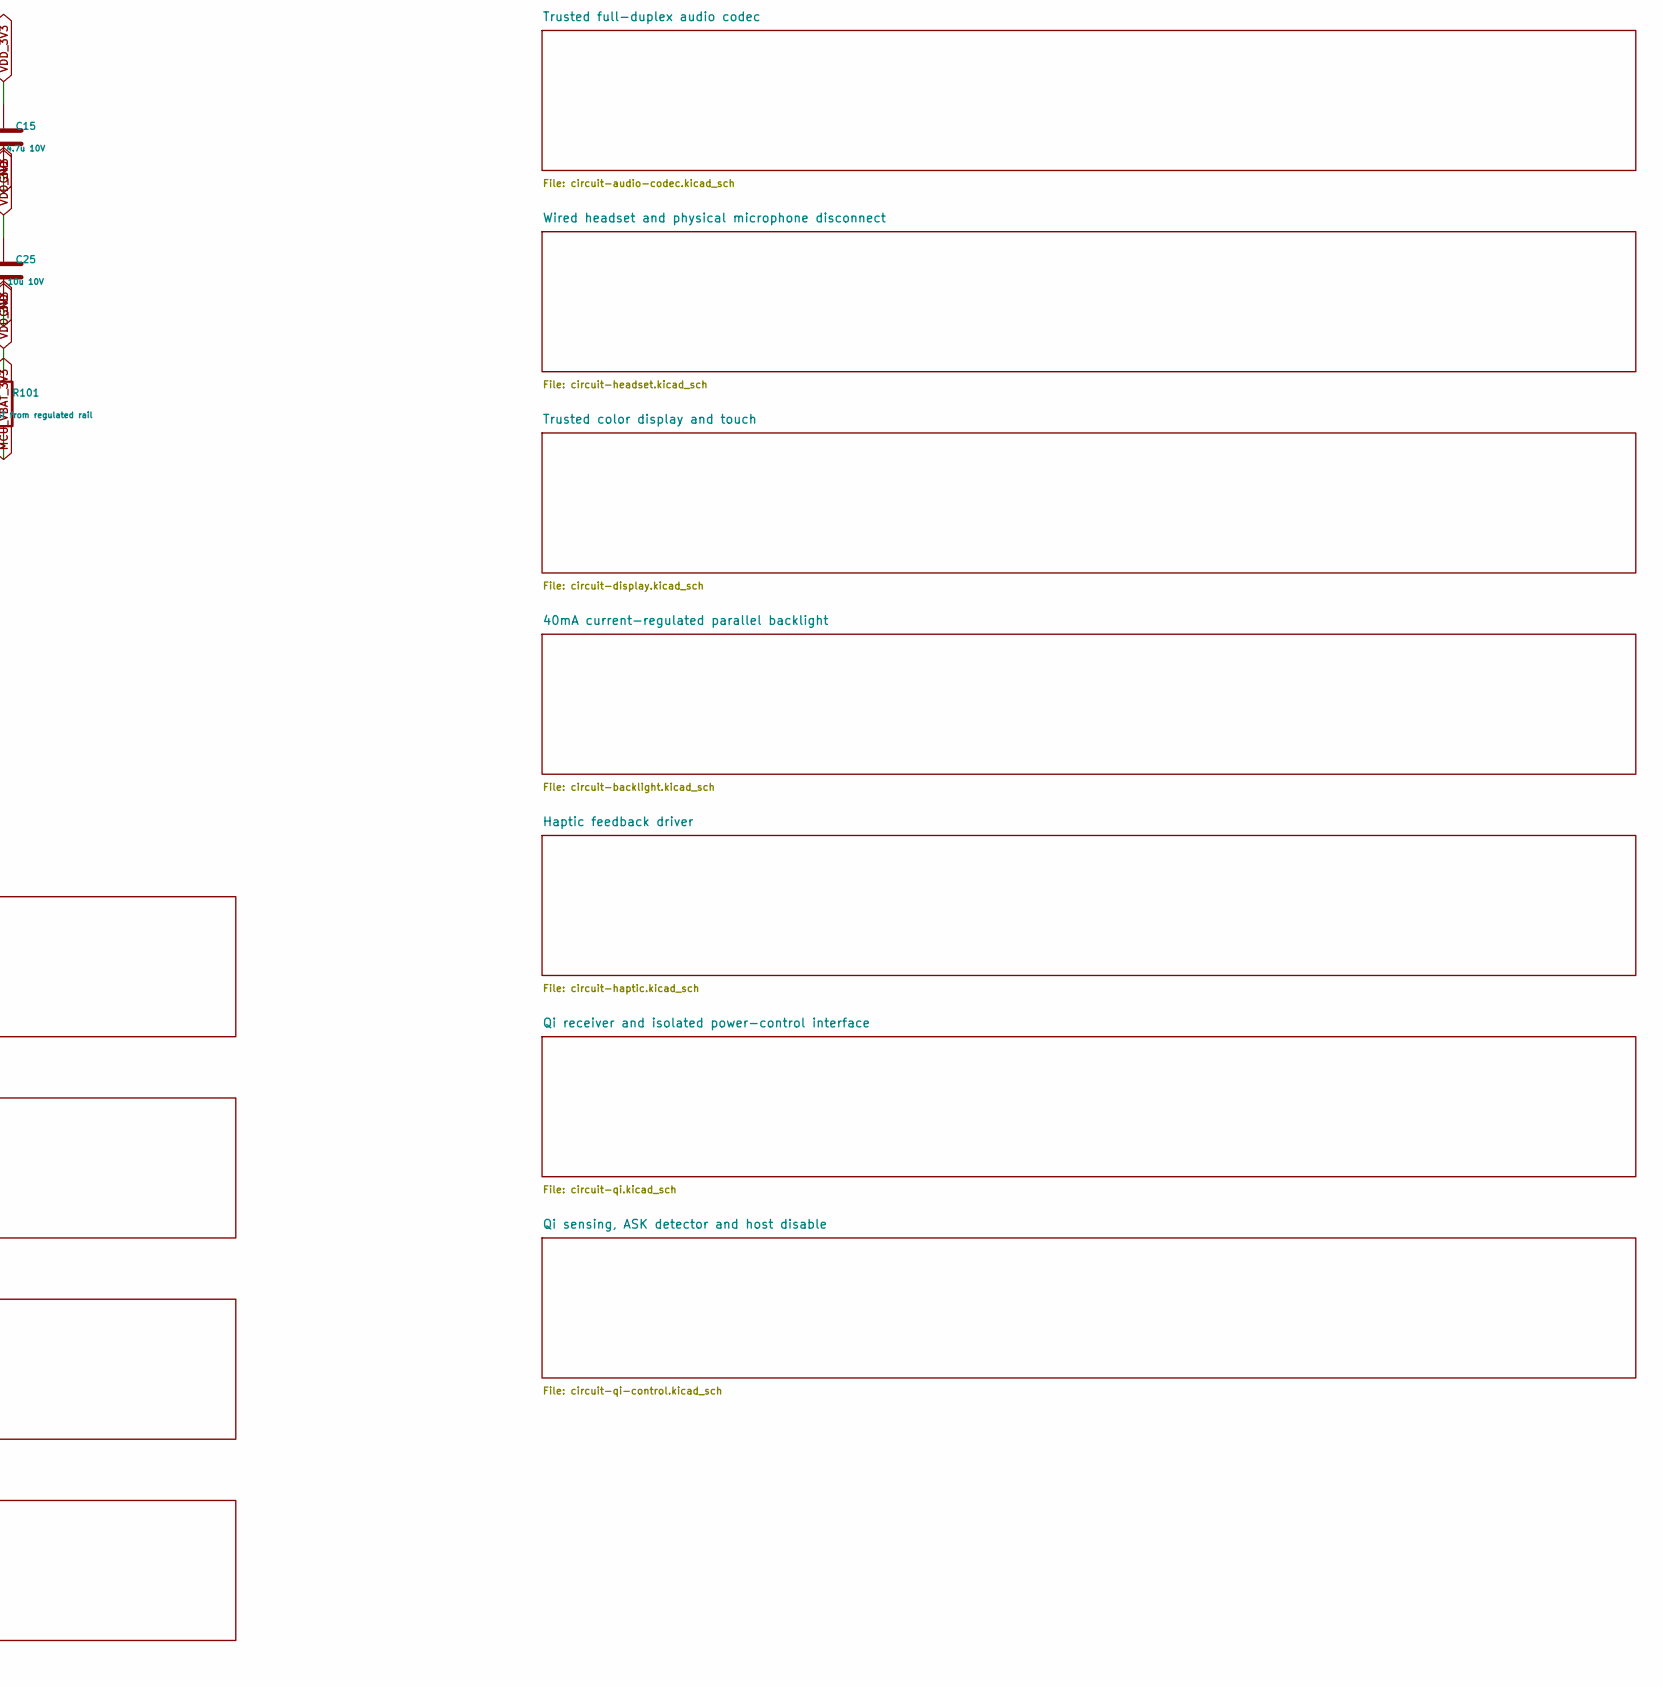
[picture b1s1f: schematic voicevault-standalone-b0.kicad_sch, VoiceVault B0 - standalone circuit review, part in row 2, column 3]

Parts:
C6, C15, C19, C109: 4.7u 10V; C_0603_1608Metric
C7, C8, C9, C10, C11, C12, C13, C14, C16, C17, C18, C20, C21, C22, C23, C24, C26, C112: 100n 10V; C_0402_1005Metric
C25, C108: 10u 10V; C_0805_2012Metric
C27, C107: 2.2u 10V; C_0603_1608Metric
C110, C111: 1u 10V; C_0603_1608Metric
J101: FTSH-107-01-L-DV / STDC14; Samtec_FTSH-107-01-L-DV
L1: VLS252012HBX-2R2M-1 / 2.2uH; L_1008_2520Metric
R101: 0R - VBAT from regulated rail; R_0402_1005Metric
U1: STM32U5G9ZJJ6Q; UFBGA-144_10x10mm_Layout12x12_P0.8mm

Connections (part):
AUD_ADC_DATA: U1.B2 (PE3); also elsewhere on the board
AUD_BCLK: U1.C4 (PE5); also elsewhere on the board
AUD_DAC_DATA: U1.D3 (PE6); also elsewhere on the board
AUD_MCLK: U1.B1 (PE2); also elsewhere on the board
AUD_POWER_EN: U1.K8 (PB10); also elsewhere on the board
AUD_RESET_N: U1.A4 (PB6); also elsewhere on the board
AUD_SCL: U1.F4 (PF1); also elsewhere on the board
AUD_SDA: U1.E5 (PF0); also elsewhere on the board
AUD_WCLK: U1.C3 (PE4); also elsewhere on the board
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
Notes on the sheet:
VOICEVAULT B0 | STANDALONE SECURE AUDIO ENDPOINT | CIRCUIT REVIEW
NOT FOR FABRICATION. Hierarchical circuits under review; all PCB routing remains incomplete.
STDC14 pin 3 is target voltage sense, NOT a power input.
Use an external STLINK-V3MINIE. Target supply is separate.
Pins 13/14 use TARGET RX/TX naming. UART6 on PC8/PC9.
Power, radio, secure elements, controls and offline-update interfaces: see child sheets.
Main debug and radio debug are separate; probes measure target voltage only.
Display/touch, haptic, Qi and NFC are on separate reviewed-source circuit sheets.
Audio codec, CTIA headset, physical microphone disconnect and microSD are additions.
Prototype has open debug access and public diagnostic material. Physical security remains unqualified.
Safe 7 source: TS7 rev_D, STM32U5G9ZJJ6Q / UFBGA144. New PCB outline is provisional 70 x 45 mm.

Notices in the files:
hardware/rev-b/README.md:
Sources and licensing:
[Source manifest](reference/source-manifest.json), pinned ST ball data, manufacturer-source hashes and [library notices](LIBRARY_NOTICE.md) accompany the design. The new hardware adaptation uses [CERN-OHL-S-2.0](LICENSE); upstream and component-library notices retain their own terms. VoiceVault is independent and has no Trezor endorsement.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
